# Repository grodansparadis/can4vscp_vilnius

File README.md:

<h1>Vilnius A/D module</h1>

Vilnius A/D module is a CAN4VSCP based module that have four 10-bit A/D channels for 0-5V or 0-10V and also have two 5V I/O channels that can be set as inputs or outputs. General use is to read analog values and as all other VSCP modules you can get the readings reported automatically with a user specified period.

It is also possible to report A/D readings as a VSCP measurement linearized as a floating point value from the formula

measurement = k * A/D-value + m

where k and m are configurable 32-bit floating point constants. You have full control of which event is sent and which unit is used.

This means you can send out any A/D reading as a real unit such as voltage, temperature or in any other SI specified unit.

You can also assign alarm limits so that alarm events are sent when the level goes above a certain value or below a certain value.

Two I/O channels are available. Both can individually be set as inputs or outputs. ON/OFF or TurnOn/TurnOff events can be sent out when I/O change state.

The module can be attached to a standard DIN Rail or be mounted directly on a wall. The mounting enclosures are ordered as separate options when the module is ordered.

The module fully adopts to the VSCP CAN4VSCP specification and can be powered directly over the bus cable with a good 9-28V DC power source. This means there is no need for a separate power cable. VSCP CAN modules are designed to work on a VSCP4CAN bus which use ordinary RJ-45 connectors or use the daisy chain pinhead which can be used to connect modules that are mounted close to each other. For the bus a CAT5 or better twisted pair cable is used. Bus length can have a total length of 500 meters with drops of maximum 24 meters length (up to a total of 120 meters). As for all VSCP4CAN modules the communication speed is fixed at 125 kbps.

All VSCP modules contains information of there own setup, manual, hardware version, manufacturer etc. When VSCP modules are started up they have a default functionality that often is all that is needed to get a working setup. If the module have something to report it will send you an event and if it is setup to react on a certain type of event it will do it's work when you send event(s) to it. It does not need to be harder then that. 

<hr>

This project is part of the <a href="http://www.vscp.org">VSCP (Very Simple Control Protocol) project</a>. 

<hr>

This project is licensed under the 
<a href="http://creativecommons.org/licenses/by-nc-sa/3.0/">Creative Commons open source license Attribution-NonCommercial-ShareAlike 3.0 Unported</a>. 
Other license options are available by conacting <a href="malto:info@grodansparadis.com">Paradis of the Frog AB</a>

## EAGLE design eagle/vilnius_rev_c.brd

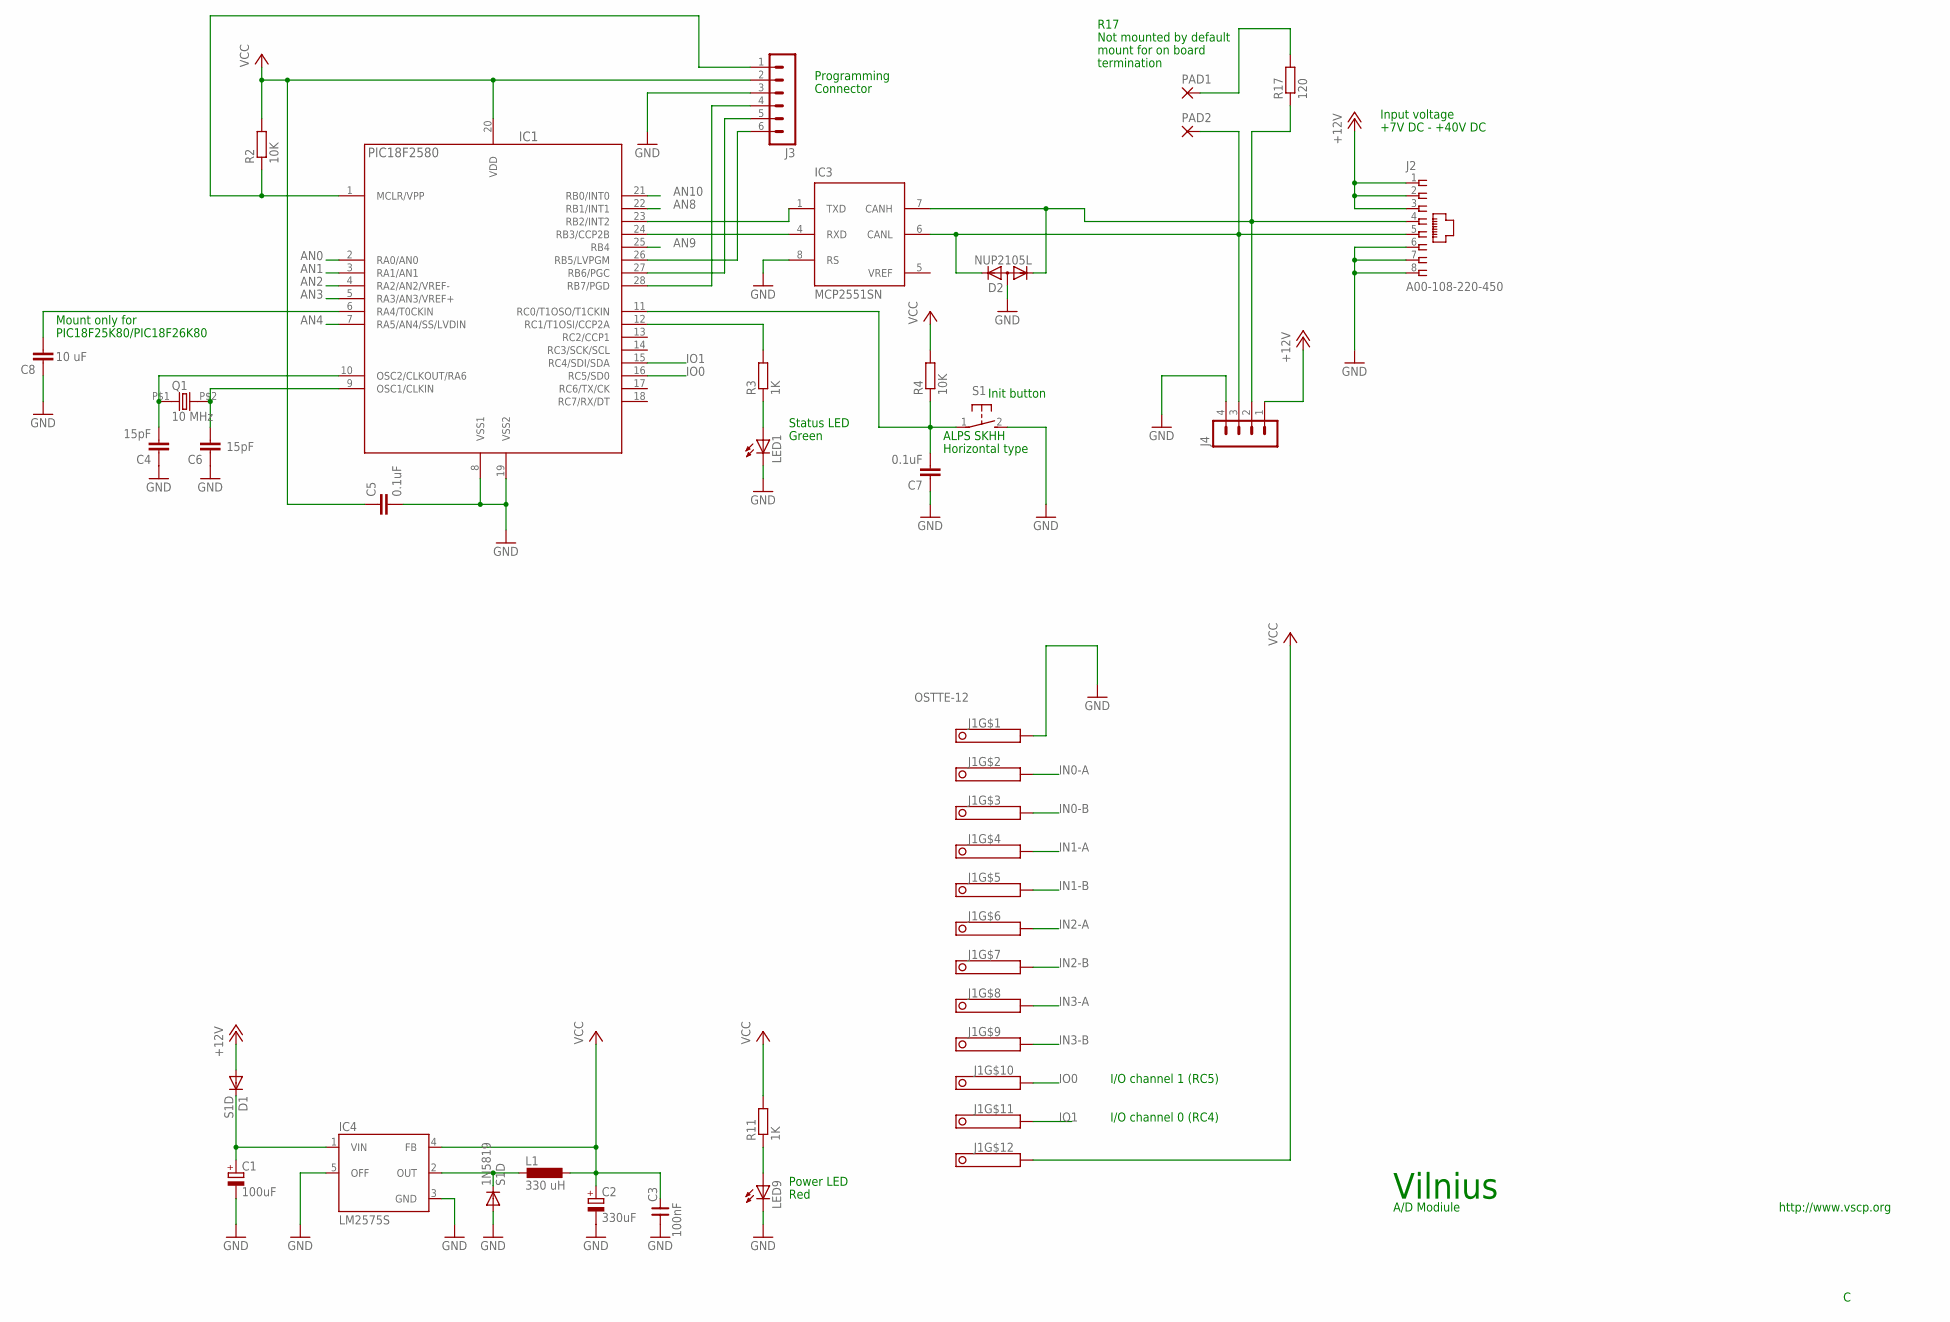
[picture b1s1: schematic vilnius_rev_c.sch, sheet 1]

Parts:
1N5819: S1D; SOD123
C1: 100uF; PANASONIC_D
C2: 330uF; PANASONIC_D
C3: 100nF; 0805
C4, C6: 15pF; C0805
C5, C7: 0.1uF; C0805
C8: 10 uF; C0805
D1: S1D; SOD123
D2: NUP2105L; SOT23@1
IC1: PIC18F2580; SO28
IC3: MCP2551SN; SO-08
IC4: LM2575S; TO263-5
J1: OSTTE-12; PINHEAD-12
J2: A00-108-220-450; RJ-45
J3: MA06-1
J4: MA04-1
L1: 330 uH; DO3316P
LED1, LED9: LEDCHIP-LED0805; CHIP-LED0805
PAD1, PAD2: 1,6/0,8
Q1: 10 MHz; 9C
R2, R4: 10K; R0805
R3, R11: 1K; R0805
R17: 120; R0805
S1: 31-XX; B3F-31XX

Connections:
+12V: D1.A, J2.1, J2.2, J2.3, J4.1
AN0: IC1.2 (RA0/AN0); also elsewhere on the board
AN1: IC1.3 (RA1/AN1); also elsewhere on the board
AN2: IC1.4 (RA2/AN2/VREF-); also elsewhere on the board
AN3: IC1.5 (RA3/AN3/VREF+); also elsewhere on the board
AN4: IC1.7 (RA5/AN4/SS/LVDIN)
AN8: IC1.22 (RB1/INT1)
AN9: IC1.25 (RB4)
AN10: IC1.21 (RB0/INT0)
CANL: D2.2 (K2), IC3.6 (CANL), J2.5, J4.3, PAD2.1
GND: 1N5819.A, C1.-, C2.-, C3.1, C4.1, C5.2, C6.1, C7.1, C8.1, D2.3 (A), IC1.8 (VSS1), IC1.19 (VSS2), IC3.2 (VSS), IC3.8 (RS), IC4.3 (GND), IC4.5 (OFF), J1.1, J2.6, J2.7, J2.8, J3.3, J4.4, LED1.C, LED9.C, S1.2 (S); also elsewhere on the board
IN0-A: J1.2; also elsewhere on the board
IN0-B: J1.3; also elsewhere on the board
IN1-A: J1.4; also elsewhere on the board
IN1-B: J1.5; also elsewhere on the board
IN2-A: J1.6; also elsewhere on the board
IN2-B: J1.7; also elsewhere on the board
IN3-A: J1.8; also elsewhere on the board
IN3-B: J1.9; also elsewhere on the board
IO0: IC1.16 (RC5/SD0), J1.10
IO1: IC1.15 (RC4/SDI/SDA), J1.11
unnamed: 1N5819.C, IC4.2 (OUT), L1.1
unnamed: C4.2, IC1.10 (OSC2/CLKOUT/RA6), Q1.P$1 (1)
unnamed: C1.+, D1.C, IC4.1 (VIN)
unnamed: IC1.12 (RC1/T1OSI/CCP2A), R3.2
unnamed: LED1.A, R3.1
unnamed: C7.2, IC1.11 (RC0/T1OSO/T1CKIN), R4.1, S1.1
unnamed: C6.2, IC1.9 (OSC1/CLKIN), Q1.P$2 (2)
unnamed: C8.2, IC1.6 (RA4/T0CKIN)
unnamed: PAD1.1, R17.2
unnamed: IC1.1 (MCLR/VPP), J3.1, R2.1
unnamed: IC1.28 (RB7/PGD), J3.4
unnamed: IC1.27 (RB6/PGC), J3.5
unnamed: IC1.26 (RB5/LVPGM), J3.6
unnamed: LED9.A, R11.1
unnamed: D2.1 (K1), IC3.7 (CANH), J2.4, J4.2, R17.1
RXCAN: IC1.24 (RB3/CCP2B), IC3.4 (RXD)
TXCAN: IC1.23 (RB2/INT2), IC3.1 (TXD)
VCC: C2.+, C3.2, C5.1, IC1.20 (VDD), IC3.3 (VDD), IC4.4 (FB), J1.12, J3.2, L1.2, R2.2, R4.2, R11.2; also elsewhere on the board
VREF: IC3.5 (VREF)

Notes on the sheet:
Init button
Status LED
Programming
Connector
ALPS SKHH
Horizontal type
Vilnius
http://www.vscp.org
A/D Modiule
Input voltage
+7V DC - +40V DC
Power LED
Red
Green
Mount only for
PIC18F25K80/PIC18F26K80
Not mounted by default
mount for on board
termination
R17
I/O channel 0 (RC4)
I/O channel 1 (RC5)

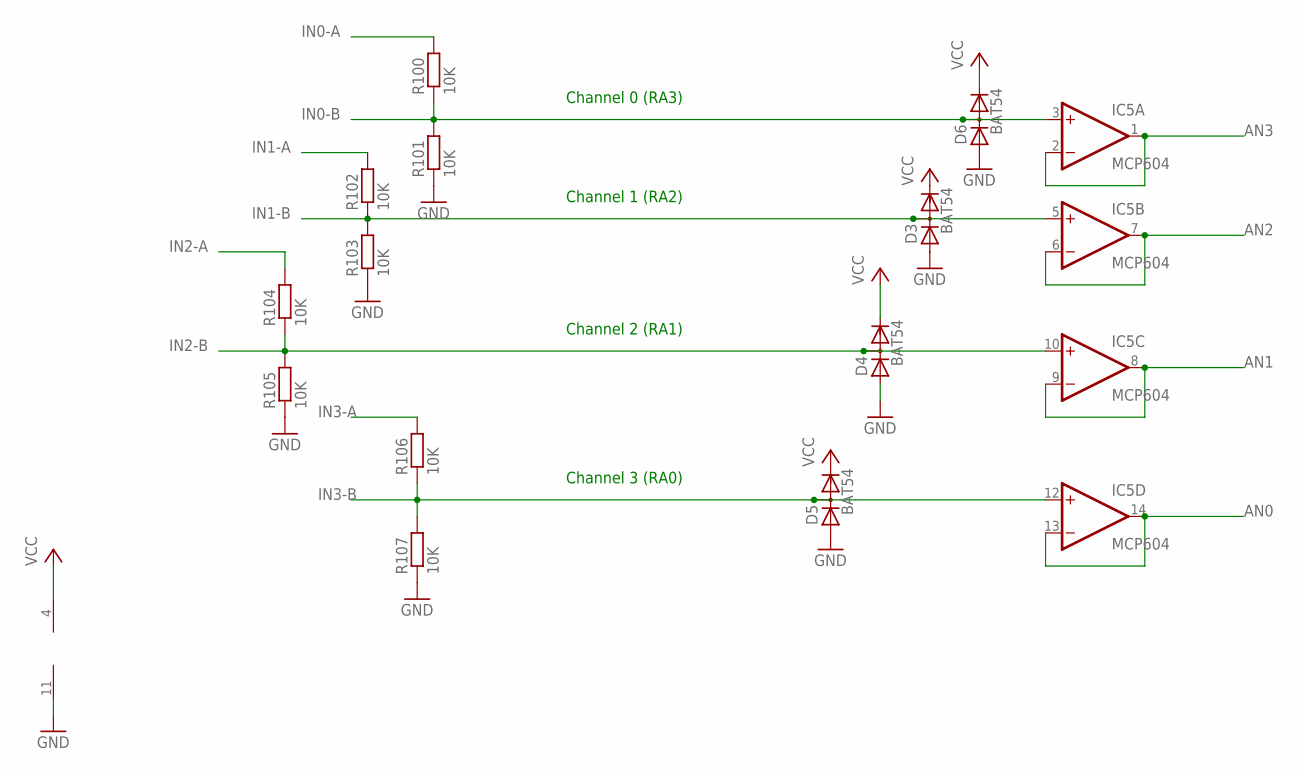
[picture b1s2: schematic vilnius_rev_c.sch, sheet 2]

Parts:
D3, D4, D5, D6: BAT54; SOT23
IC5: MCP604; SO14
R100, R101, R102, R103, R104, R105, R106, R107: 10K; R0805

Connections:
AN0: IC5.13 (-IN), IC5.14 (OUT); also elsewhere on the board
AN1: IC5.8 (OUT), IC5.9 (-IN); also elsewhere on the board
AN2: IC5.6 (-IN), IC5.7 (OUT); also elsewhere on the board
AN3: IC5.1 (OUT), IC5.2 (-IN); also elsewhere on the board
GND: D3.1 (A), D4.1 (A), D5.1 (A), D6.1 (A), IC5.11 (V-), R101.1, R103.1, R105.1, R107.1; also elsewhere on the board
IN0-A: R100.2; also elsewhere on the board
IN0-B: D6.3 (AC), IC5.3 (+IN), R100.1, R101.2; also elsewhere on the board
IN1-A: R102.2; also elsewhere on the board
IN1-B: D3.3 (AC), IC5.5 (+IN), R102.1, R103.2; also elsewhere on the board
IN2-A: R104.2; also elsewhere on the board
IN2-B: D4.3 (AC), IC5.10 (+IN), R104.1, R105.2; also elsewhere on the board
IN3-A: R106.2; also elsewhere on the board
IN3-B: D5.3 (AC), IC5.12 (+IN), R106.1, R107.2; also elsewhere on the board
VCC: D3.2 (C), D4.2 (C), D5.2 (C), D6.2 (C), IC5.4 (V+); also elsewhere on the board

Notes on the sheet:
Channel 0 (RA3)
Channel 1 (RA2)
Channel 2 (RA1)
Channel 3 (RA0)

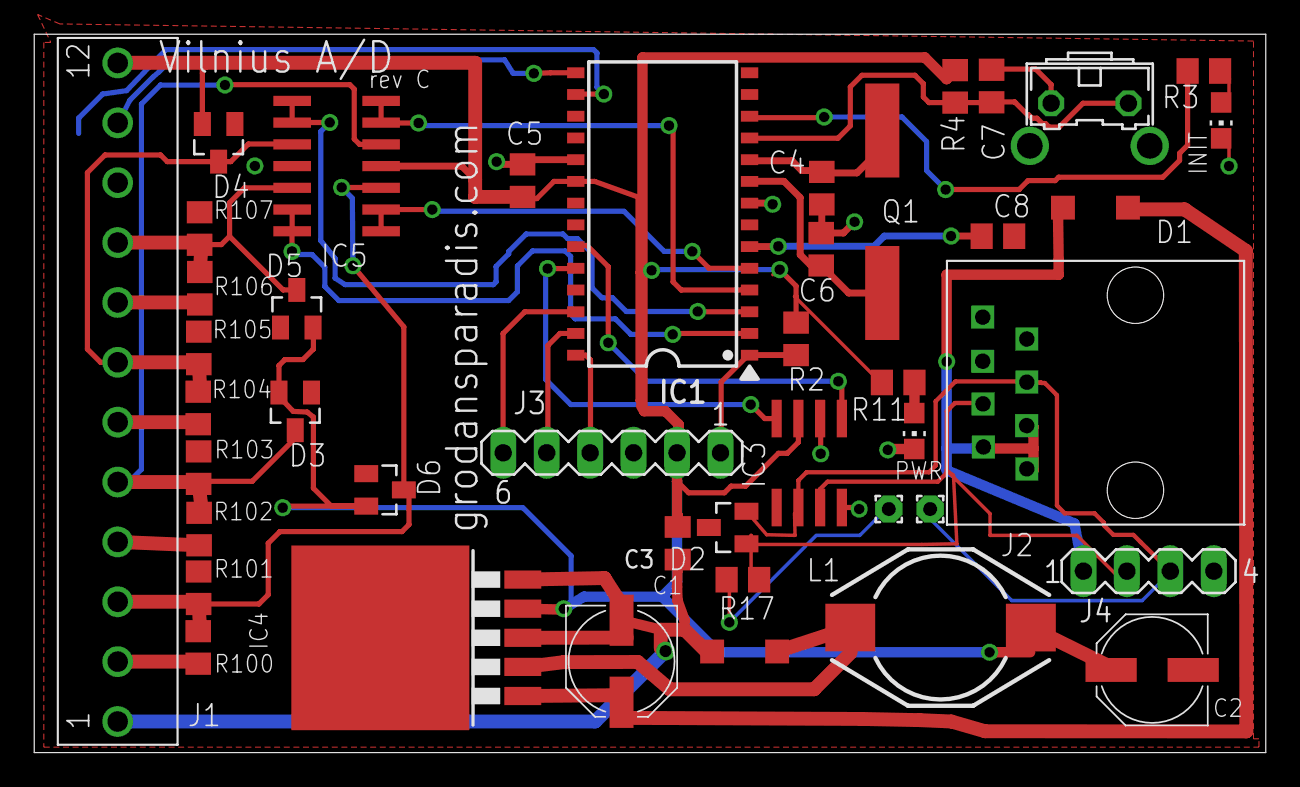
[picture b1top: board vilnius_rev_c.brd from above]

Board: 2 copper layers, 72.0 x 42.0 mm, 43 parts (0 on the bottom side), 35 nets.

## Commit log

2015-06-15 Initial checkin
2015-08-17 Changed license to Artistic License 3.0
2015-11-13 Added firmware readme to Vilnius
2015-11-14 AKHE VCAP decoupled from VCC
2015-11-30 Added initial project
2015-11-30 Updated project file
2015-12-07 Main functionality in place
2015-12-08 I/O event handling in place
2015-12-09 Linear measurement adoption in place
2015-12-10 Debug of alarms. Works now
2015-12-15 SYNC handling added
2015-12-17 Updated license file
2015-12-17 Changed copyright info in headers so it is correct
2015-12-22 Added to ignores
2016-03-04 Version 1.0.0
2016-03-04 Added picture
2016-03-08 Adopted to 1.6 firmware. Adopted for PIC18F26K80.
2016-03-08 Fixed copyright info
2016-03-23 Fixed bug in control byte write routine
2016-03-23 Version 1.0.3
2016-04-04 Changed value of C14 to 10uF
2016-04-19 RA4 set to input to prevent collision with VCAP circuits in PIC18F2580. Brown out raised to maximum (3V & 4.6V). Valuable input from Anders Forsgren, AJE Electronics AB.
2016-05-04 Added new link to bit timing
2018-06-11 Updated paths for firmware, picture and manual
2020-05-15 init timeout set to 2500 ms
2020-05-15 Updated firmware
2020-11-22 Fixed errors in mdf
2024-04-19 DM matrix pointer to register page 3 should be 2
2024-04-19 Updated MDF version
2024-04-19 DM on page 3 in header is wrong, should be 2
